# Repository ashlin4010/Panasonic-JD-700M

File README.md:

# Panasonic JD-700M #

This repository contains notes and test applications I used to fix a Panasonic JD-700M

## logic_board ##
This folder contains a PCB to adapt the video output from the Panasonic to composite.
The previous owner had hacked this on, no doubt it could be done better.

## logic_board ##
Is some schematic specifically around the memory section.

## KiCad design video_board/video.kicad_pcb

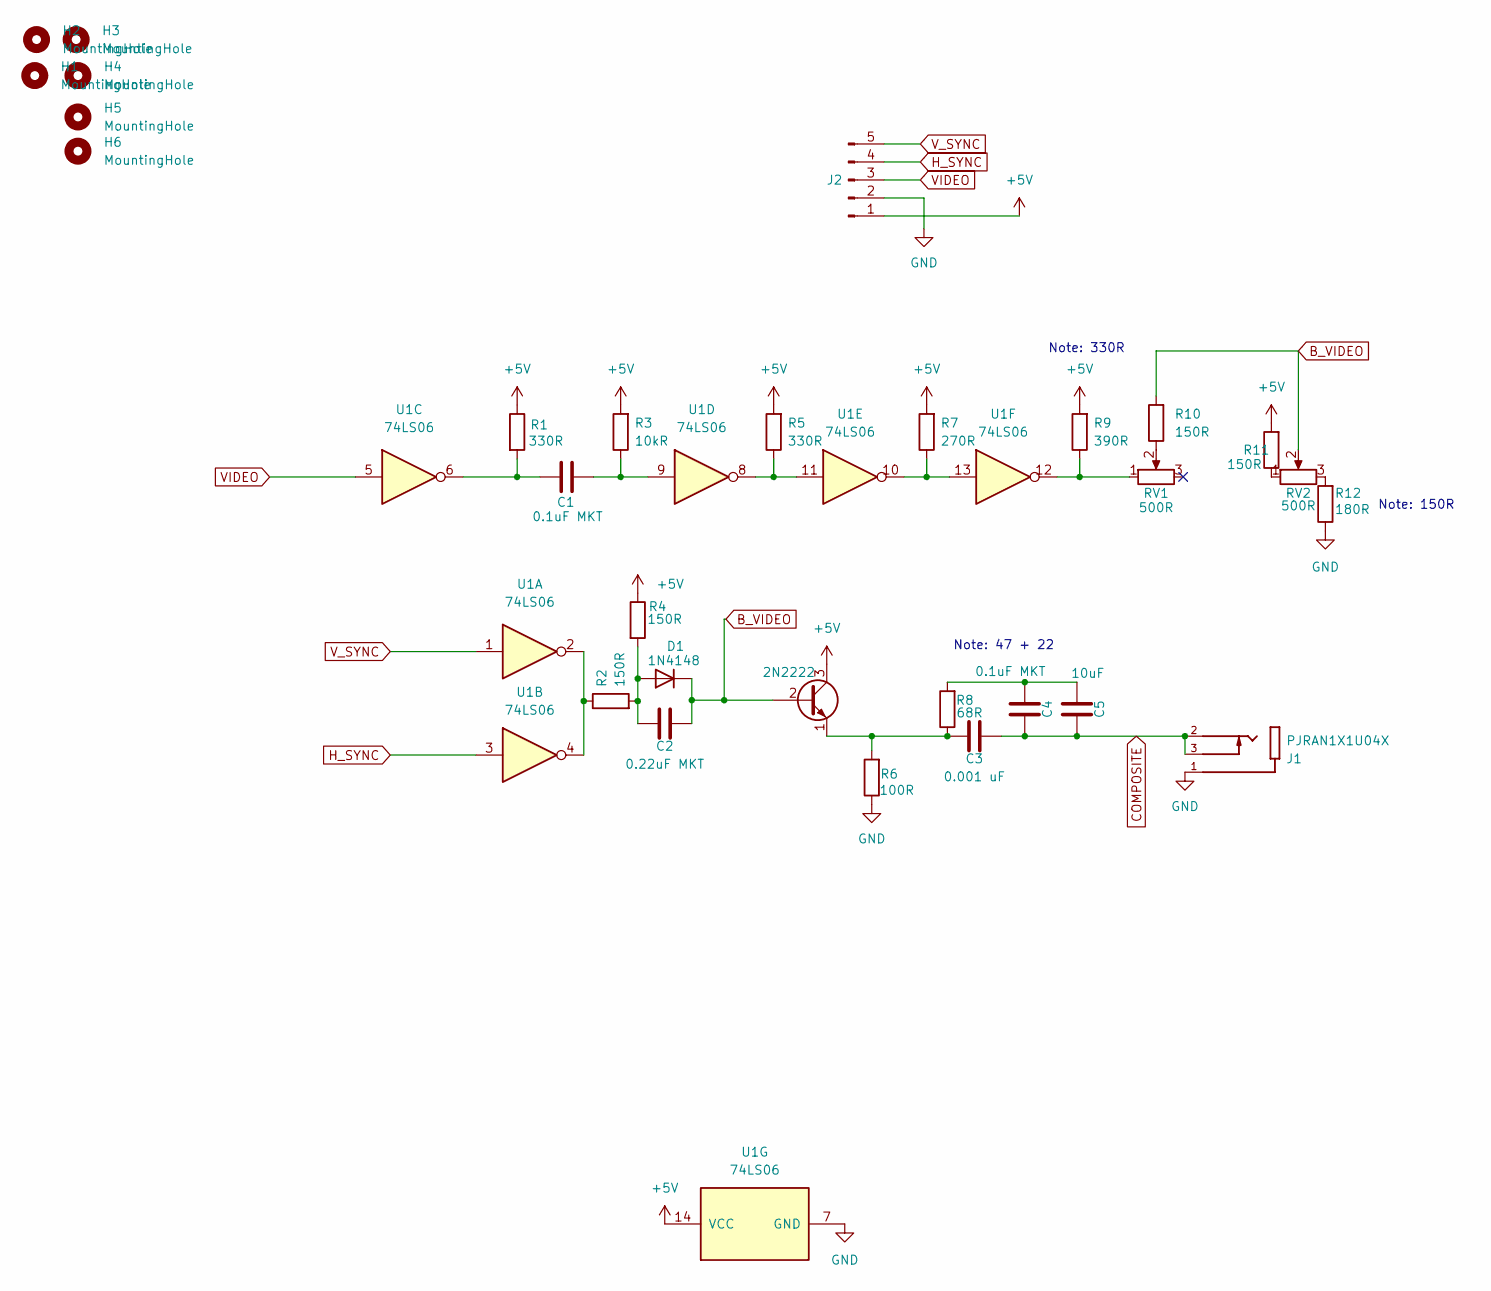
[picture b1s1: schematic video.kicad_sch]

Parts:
C1, C4: 0.1uF MKT; C_Disc_D3.0mm_W1.6mm_P2.50mm
C2: 0.22uF MKT; C_Disc_D3.0mm_W1.6mm_P2.50mm
C3: 0.001 uF; C_Disc_D3.0mm_W1.6mm_P2.50mm
C5: 10uF; C_Disc_D3.0mm_W1.6mm_P2.50mm
D1: 1N4148; D_DO-35_SOD27_P7.62mm_Horizontal
H1, H2, H3, H4, H5, H6: MountingHole; MountingHole_3.2mm_M3
J1: PJRAN1X1U04X; SWITCHCRAFT_PJRAN1X1U04X; PARTREV A
J2: Conn_01x05_Male; PinHeader_1x05_P2.54mm_Vertical
Q1: 2N2222; TO-92L
R1, R5: 330R; R_Axial_DIN0207_L6.3mm_D2.5mm_P7.62mm_Horizontal
R2, R4, R10, R11: 150R; R_Axial_DIN0207_L6.3mm_D2.5mm_P7.62mm_Horizontal
R3: 10kR; R_Axial_DIN0207_L6.3mm_D2.5mm_P7.62mm_Horizontal
R6: 100R; R_Axial_DIN0207_L6.3mm_D2.5mm_P7.62mm_Horizontal
R7: 270R; R_Axial_DIN0207_L6.3mm_D2.5mm_P7.62mm_Horizontal
R8: 68R; R_Axial_DIN0207_L6.3mm_D2.5mm_P7.62mm_Horizontal
R9: 390R; R_Axial_DIN0207_L6.3mm_D2.5mm_P7.62mm_Horizontal
R12: 180R; R_Axial_DIN0207_L6.3mm_D2.5mm_P7.62mm_Horizontal
RV1, RV2: 500R; Potentiometer_Piher_PT-10-V10_Vertical
U1: 74LS06; DIP-14_W7.62mm_Socket

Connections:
+5V: J2.1, Q1.3 (C), R1.1, R3.2, R4.1, R5.2, R7.2, R9.2, R11.2, U1.14 (VCC)
B_VIDEO: C2.2, D1.1 (K), Q1.2 (B), R10.2, RV2.2
COMPOSITE: C3.2, C4.1, C5.1, J1.2, J1.3
GND: J1.1, J2.2, R6.1, R12.1, U1.7 (GND)
H_SYNC: J2.4, U1.3
unnamed: C1.1, R1.2, U1.6
unnamed: C1.2, R3.1, U1.9
unnamed: C4.2, C5.2, R8.2
unnamed: C2.1, D1.2 (A), R2.2, R4.2
unnamed: C3.1, Q1.1 (E), R6.2, R8.1
unnamed: R2.1, U1.2, U1.4
unnamed: R5.1, U1.8, U1.11
unnamed: R7.1, U1.10, U1.13
unnamed: R9.1, RV1.1, U1.12
unnamed: R10.1, RV1.2
unnamed: R11.1, RV2.1
unnamed: R12.2, RV2.3
VIDEO: J2.3, U1.5
V_SYNC: J2.5, U1.1

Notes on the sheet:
Note: 47 + 22
Note: 150R
Note: 330R

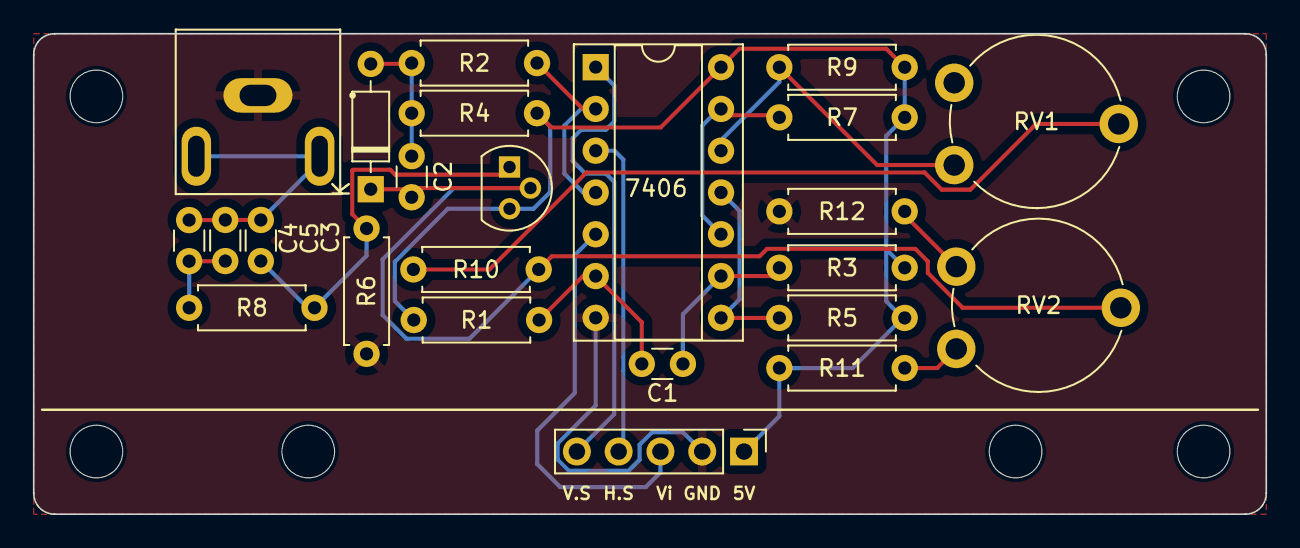
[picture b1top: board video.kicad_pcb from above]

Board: 2 copper layers, 74.9 x 29.2 mm, 30 parts (0 on the bottom side), 19 nets.

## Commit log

2024-07-05 init
2024-07-05 Added video board
